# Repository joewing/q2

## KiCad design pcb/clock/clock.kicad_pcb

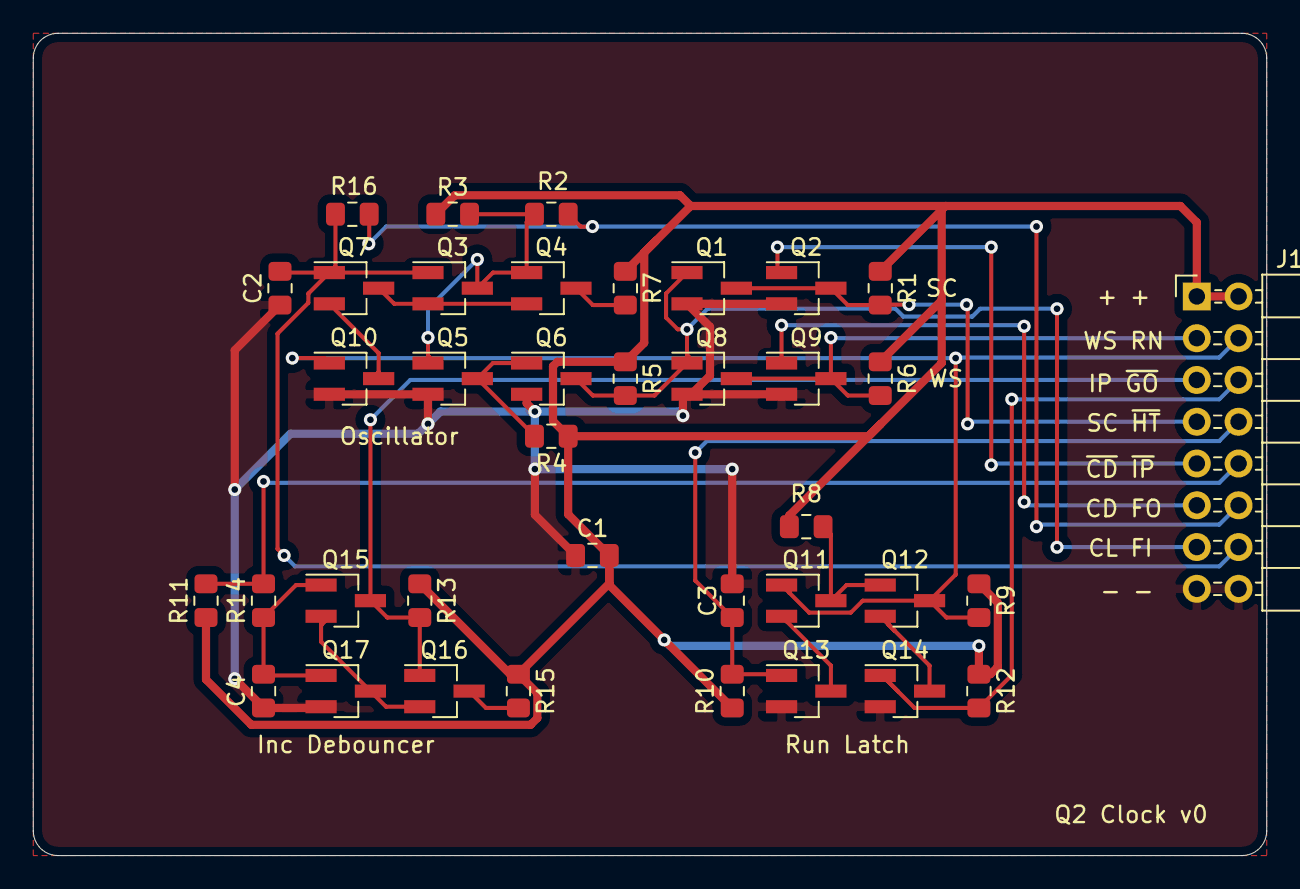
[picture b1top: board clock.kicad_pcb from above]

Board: 2 copper layers, 75.0 x 50.0 mm, 38 parts (0 on the bottom side), 25 nets.

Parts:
C1, C2, C3, C4: 0.1u; C_0805_2012Metric_Pad1.15x1.40mm_HandSolder
J1: Conn_02x08_Odd_Even; PinHeader_2x08_P2.54mm_Horizontal
Q1, Q2, Q3, Q4, Q5, Q6, Q7, Q8, Q9, Q10, Q11, Q12, Q13, Q14, Q15, Q16, Q17: 2N7002; SOT-23_Handsoldering
R1, R2, R3, R4, R5, R6, R7, R8, R9, R10, R11, R12, R13, R14, R15: 10k; R_0805_2012Metric_Pad1.15x1.40mm_HandSolder
R16: 1m; R_0805_2012Metric_Pad1.15x1.40mm_HandSolder

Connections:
CDIV: J1.11, Q9.1
CLK: J1.13, Q1.1, Q6.3, Q8.1, R5.2
FAST_IN: C2.2, J1.14, Q3.1, Q7.1, R16.2
FAST_OUT: J1.12, R2.1, R16.1
GND: C1.1, C2.1, C3.1, C4.1, J1.15, J1.16, Q1.2, Q2.2, Q5.2, Q6.2, Q8.2, Q9.2, Q10.2, Q13.2, Q14.2, Q17.2
INCP_DB: J1.5, Q15.3, Q16.1, R13.2
unnamed: C4.2, Q15.1, Q17.1, R14.1
unnamed: Q3.2, Q4.2, Q7.3
unnamed: Q3.3, Q4.1, Q5.1, R2.2, R3.2
unnamed: Q4.3, R7.2
unnamed: Q5.3, Q6.1, R4.2
unnamed: Q7.2, Q10.3
unnamed: Q11.2, Q13.3
unnamed: Q11.3, Q12.1, R8.2
unnamed: Q12.2, Q14.3
unnamed: Q15.2, Q16.2, Q17.3
unnamed: Q16.3, R15.2
RUN: J1.4, Q10.1, Q11.1, Q12.3, R9.2
SC: J1.7, Q1.3, Q2.3, R1.2
VCC: C1.2, J1.1, J1.2, R1.1, R3.1, R4.1, R5.1, R6.1, R7.1, R8.1, R9.1, R10.1, R11.1, R12.1, R13.1, R15.1
WS: J1.3, Q8.3, Q9.3, R6.2
~CDIV: J1.9, Q2.1
~INCP_SW: J1.10, R11.2, R14.2
~START_SW: J1.6, Q14.1, R12.2
~STOP_SW: C3.2, J1.8, Q13.1, R10.2

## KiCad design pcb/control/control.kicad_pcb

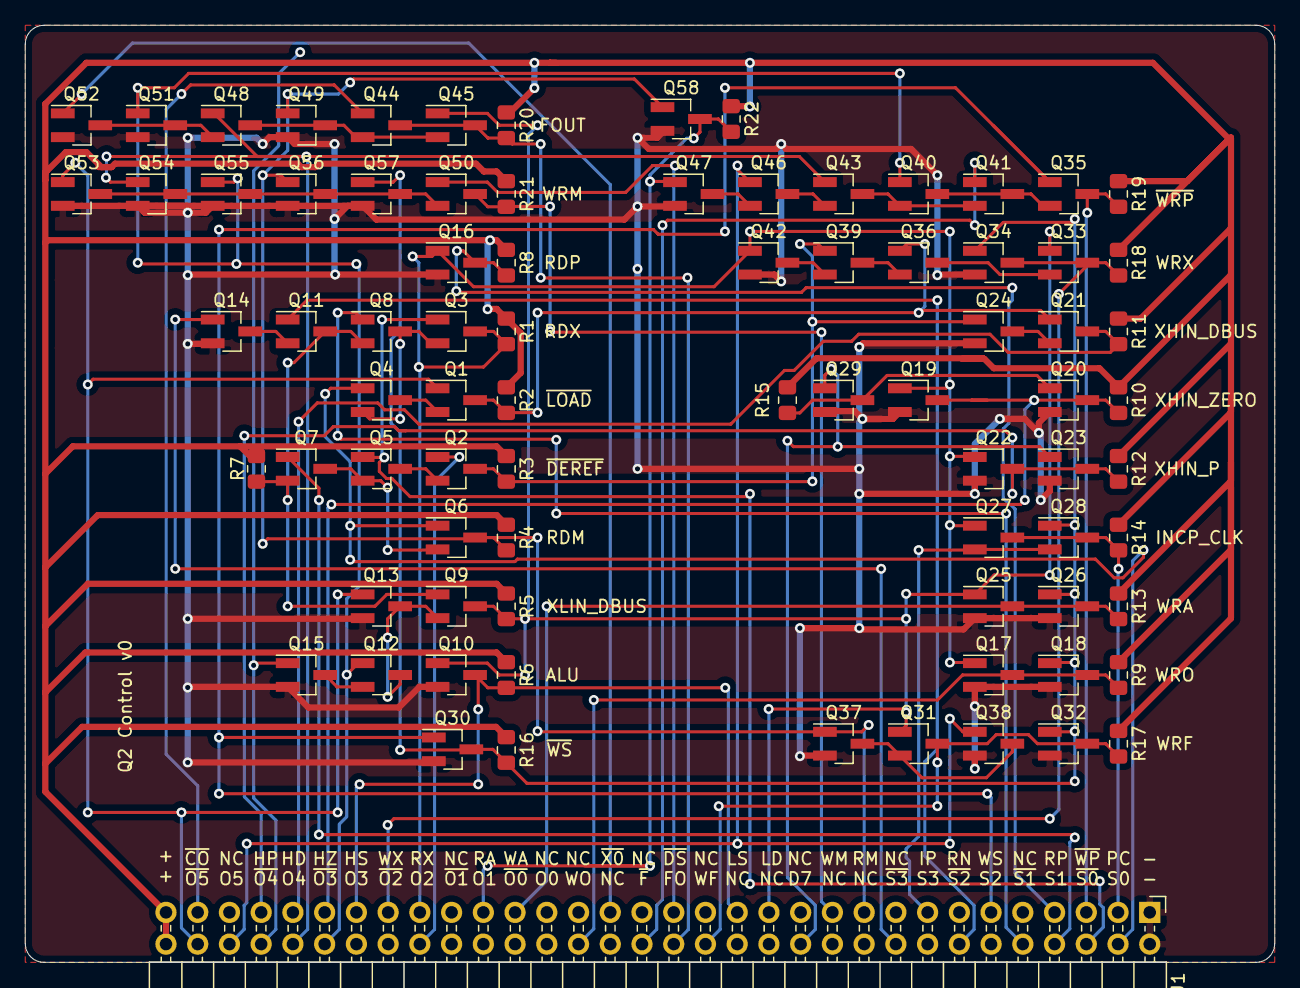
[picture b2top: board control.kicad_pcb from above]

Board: 2 copper layers, 100.0 x 75.0 mm, 81 parts (0 on the bottom side), 62 nets.

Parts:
J1: Conn_02x32_Odd_Even; PinHeader_2x32_P2.54mm_Horizontal
Q1, Q2, Q3, Q4, Q5, Q6, Q7, Q8, Q9, Q10, Q11, Q12, Q13, Q14, Q15, Q16, Q17, Q18, Q19, Q20, Q21, Q22, Q23, Q24, Q25, Q26, Q27, Q28, Q29, Q30, Q31, Q32, Q33, Q34, Q35, Q36, Q37, Q38, Q39, Q40, Q41, Q42, Q43, Q44, Q45, Q46, Q47, Q48, Q49, Q50, Q51, Q52, Q53, Q54, Q55, Q56, Q57, Q58: 2N7002; SOT-23_Handsoldering
R1, R2, R3, R4, R5, R6, R7, R8, R9, R10, R11, R12, R14, R15, R16, R17, R18, R19, R20, R21, R22: 10k; R_0805_2012Metric_Pad1.15x1.40mm_HandSolder
R13: 1k; R_0805_2012Metric_Pad1.15x1.40mm_HandSolder

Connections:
DBUS7: J1.24, Q23.1, Q29.1
FOUT: J1.32, Q44.3, Q45.3, R20.2
GND: J1.1, J1.2, Q10.2, Q13.2, Q14.2, Q15.2, Q16.2, Q17.2, Q18.2, Q19.2, Q20.2, Q22.2, Q23.2, Q24.2, Q25.2, Q26.2, Q29.2, Q30.2, Q32.2, Q34.2, Q37.2, Q38.2, Q42.2, Q47.2, Q49.2, Q51.2, Q52.2, Q53.2, Q54.2, Q55.2, Q56.2, Q57.2, Q58.2
INCP_CLK: J1.3, Q27.3, Q28.3, R14.2
INCP_DB: J1.15, Q27.2, Q28.2
unnamed: Q1.2, Q4.3
unnamed: Q2.2, Q5.3
unnamed: Q3.2, Q4.2, Q8.3
unnamed: Q5.2, Q6.2, Q7.3
unnamed: Q11.2, Q14.3
unnamed: Q7.2, Q8.2, Q9.1, Q11.3, R7.2
unnamed: Q12.2, Q15.3
unnamed: Q9.2, Q12.3, Q13.3
unnamed: Q21.2, Q24.3
unnamed: Q31.2, Q37.3, Q38.3
unnamed: Q33.2, Q36.3
unnamed: Q35.2, Q40.3, Q41.3
unnamed: Q36.2, Q39.3
unnamed: Q39.2, Q42.3
unnamed: Q40.2, Q41.2, Q43.3
unnamed: Q43.2, Q46.3
unnamed: Q44.2, Q45.2, Q48.3, Q49.3
unnamed: Q46.2, Q47.3
unnamed: Q48.2, Q51.3, Q52.3
unnamed: Q50.2, Q53.3, Q54.3, Q55.3, Q56.3, Q57.3
OP2: J1.48, Q2.1
OP4: J1.56, Q43.1, Q48.1, Q54.1
OP5: J1.60, Q38.1, Q46.1
RDA_DBUS: J1.43, Q47.1, Q58.3, R22.2
RDM: J1.19, Q6.3, Q37.1, Q49.1, Q56.1, Q58.1, R4.2
RDP_ABUS: J1.7, Q16.3, R8.2
RDX_ABUS: J1.47, Q3.3, Q16.1, Q17.1, Q19.1, Q22.1, Q27.1, Q42.1, R1.2
S0: J1.4, Q4.1, Q6.1
S1: J1.8, Q7.1
STATE_ALU: J1.27, J1.51, Q10.3, R6.2
VCC: J1.63, J1.64, R1.1, R2.1, R3.1, R4.1, R5.1, R6.1, R7.1, R8.1, R9.1, R10.1, R11.1, R12.1, R13.1, R14.1, R15.1, R16.1, R17.1, R18.1, R19.1, R20.1, R21.1, R22.1
WRA: J1.41, Q25.3, Q26.3, R13.2
WRF: J1.30, Q31.3, Q32.3, R17.2
WRM: J1.21, Q50.3, R21.2
WRO: J1.38, Q17.3, Q18.3, R9.2
WRX: J1.49, Q33.3, Q34.3, R18.2
WS: J1.11, Q30.1, Q35.1
XHIN_DBUS: J1.55, Q21.3, R11.2
XHIN_P: J1.57, Q22.3, Q23.3, R12.2
XHIN_ZERO: J1.53, Q19.3, Q20.3, R10.2
XLIN_DBUS: J1.25, Q9.3, Q10.1, Q25.1, Q31.1, Q33.1, Q45.1, R5.2
~ALU_COUT: J1.61, Q44.1
~DBUS7: Q20.1, Q29.3, R15.2
~DEP_SW: J1.31, Q50.1
~F: J1.34, Q41.1
~OP3: J1.54, Q12.1, Q40.1, Q51.1, Q55.1
~OP4: J1.58, Q15.1
~OP5: J1.62, Q1.1, Q13.1, Q53.1
~S0: J1.6, Q3.1, Q5.1
~S1: J1.10, Q8.1
~S2: J1.14, Q11.1
~S3: J1.18, Q14.1
~STATE_DEREF: Q2.3, Q24.1, Q39.1, R3.2
~STATE_LOAD: Q1.3, Q21.1, Q36.1, R2.2
~WRP: J1.5, Q35.3, R19.2
~WS: Q18.1, Q26.1, Q28.1, Q30.3, Q32.1, Q34.1, Q57.1, R16.2
~X0: J1.35, Q52.1

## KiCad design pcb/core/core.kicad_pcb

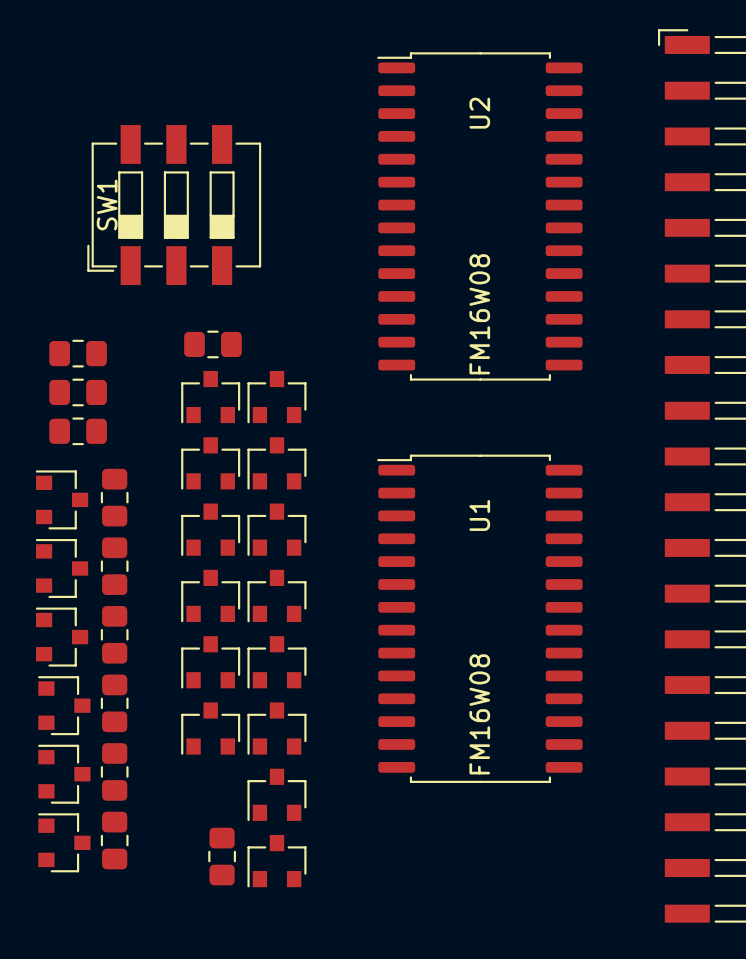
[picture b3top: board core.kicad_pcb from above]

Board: 2 copper layers, 36 parts (1 on the bottom side), 57 nets, no tracks yet.

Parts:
J1: Top; Harwin_M20-89020xx_1x20_P2.54mm_Horizontal
J2: Bottom; Harwin_M20-89020xx_1x20_P2.54mm_Horizontal
Q1, Q2, Q3, Q4, Q5, Q6, Q7, Q8, Q9, Q10, Q11, Q12, Q13, Q14, Q15, Q16, Q17, Q18, Q19, Q20: 2N7002; SOT-23
R1, R2, R3, R4, R5, R6, R7, R8, R9, R10, R11: R; R_0805_2012Metric_Pad1.15x1.40mm_HandSolder
SW1: SW_DIP_x03; SW_DIP_SPSTx03_Slide_6.7x9.18mm_W6.73mm_P2.54mm_LowProfile_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
U1, U2: FM16W08; SOIC-28W_7.5x17.9mm_P1.27mm

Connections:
A0: J1.17, U1.10, U2.10
A1: J1.16, U1.9, U2.9
A2: J1.15, U1.8, U2.8
A3: J1.14, U1.7, U2.7
A4: J1.13, U1.6, U2.6
A5: J1.12, U1.5, U2.5
A6: J1.11, U1.4, U2.4
A7: J1.10, U1.3, U2.3
A8: J1.9, U1.25, U2.25
A9: J1.8, U1.24, U2.24
A10: J1.7, U1.21, U2.21
A11: J1.6, U1.23, U2.23
A12: J1.5, U1.2, U2.2
A13: J1.4, Q8.1, Q14.1
A14: J1.3, Q9.1, Q13.1
A15: J1.2, Q4.1, Q19.1
D0: J2.4, U1.11
D1: J2.5, U1.12
D2: J2.6, U1.13
D3: J2.7, U1.15
D4: J2.8, U1.16
D5: J2.9, U1.17
D6: J2.10, U1.18
D7: J2.11, U1.19
D8: J2.12, U2.11
D9: J2.13, U2.12
D10: J2.14, U2.13
D11: J2.15, U2.15
D12: J2.16, U2.16
D13: J2.17, U2.17
D14: J2.18, U2.18
D15: J2.19, U2.19
GND: J1.20, J2.1, Q1.2, Q2.2, Q3.2, Q8.2, Q13.2, Q18.2, Q19.2, Q20.2, SW1.1, SW1.2, SW1.3, U1.14, U2.14
unnamed: Q4.2, Q6.3
unnamed: Q5.2, Q7.3
unnamed: Q10.2, Q12.3
unnamed: Q6.2, Q7.2, Q9.3, Q10.3
unnamed: Q11.2, Q12.2, Q14.3, Q15.3
unnamed: Q9.2, Q11.3
unnamed: Q14.2, Q16.3
unnamed: Q15.2, Q17.3
unnamed: Q16.2, Q17.2, Q18.3
unnamed: Q18.1, Q20.3, R11.2
S13: Q1.3, Q16.1, R1.2
S14: Q2.3, Q11.1, R2.2
S15: Q3.3, Q6.1, R3.2
VCC: J1.1, J2.20, R1.1, R2.1, R3.1, R4.1, R5.1, R6.1, R7.1, R8.1, R9.1, R10.1, R11.1, U1.28, U2.28
~A13: Q8.3, Q15.1, R8.2
~A14: Q10.1, Q13.3, R9.2
~A15: Q5.1, Q19.3, R10.2
~CE: Q4.3, Q5.3, R7.2, U1.20, U2.20
~EN: J1.18, Q20.1
~OE: J2.3, U1.22, U2.22
~S13: Q1.1, Q17.1, R4.2, SW1.6
~S14: Q2.1, Q12.1, R5.2, SW1.5
~S15: Q3.1, Q7.1, R6.2, SW1.4
~WE: J2.2, U1.27, U2.27

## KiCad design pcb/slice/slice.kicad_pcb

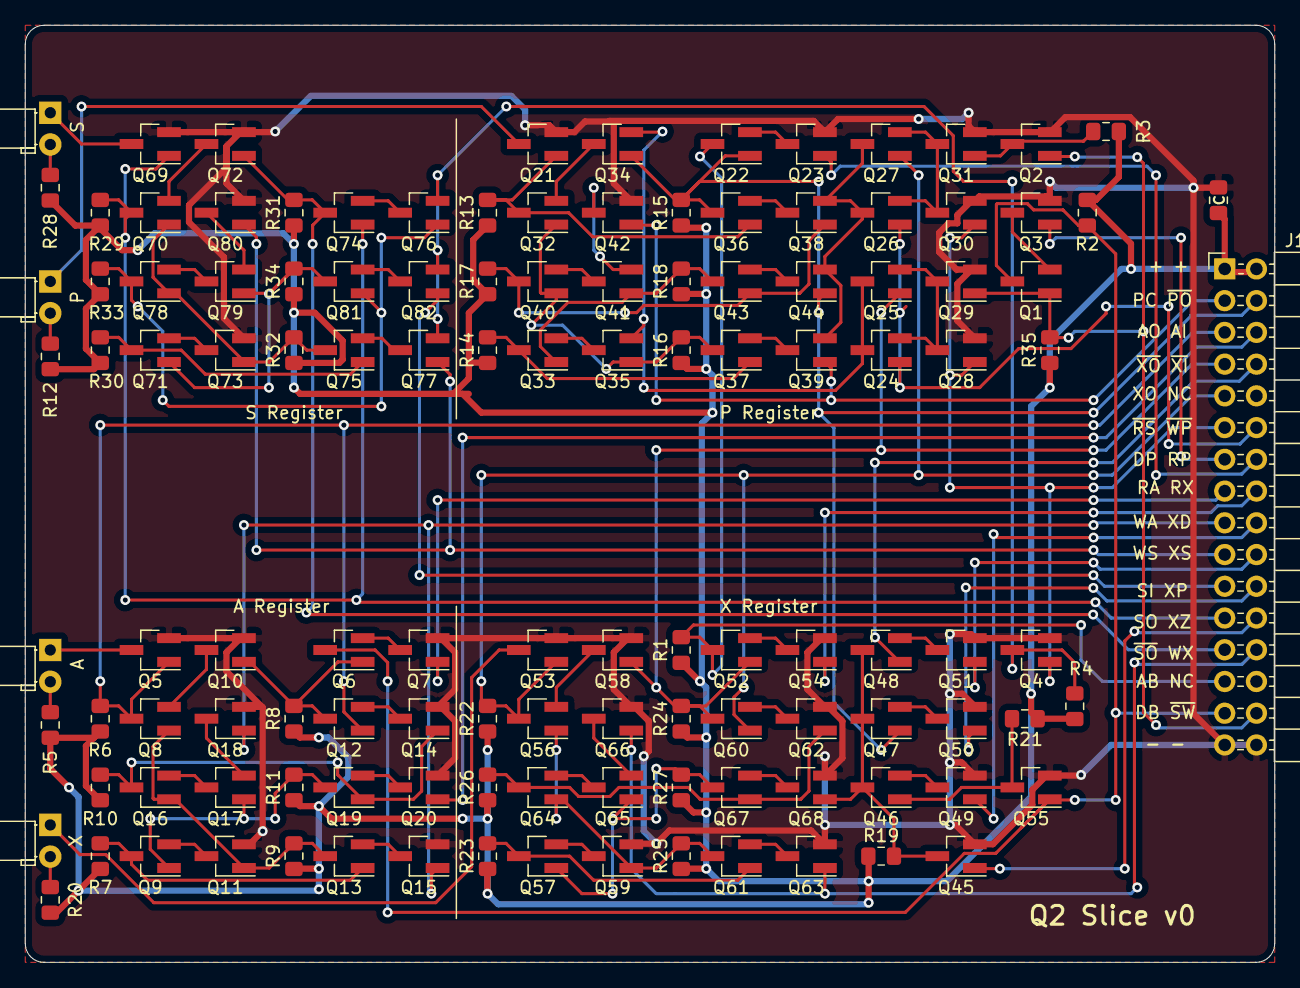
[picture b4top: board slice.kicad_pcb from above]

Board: 2 copper layers, 100.0 x 75.0 mm, 123 parts (0 on the bottom side), 97 nets.

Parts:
C1: 0.1u; C_0805_2012Metric_Pad1.15x1.40mm_HandSolder
D1: A; LED_D3.0mm_Horizontal_O1.27mm_Z2.0mm
D2: P; LED_D3.0mm_Horizontal_O1.27mm_Z2.0mm
D3: X; LED_D3.0mm_Horizontal_O1.27mm_Z2.0mm
D4: S; LED_D3.0mm_Horizontal_O1.27mm_Z2.0mm
J1: Conn_02x16_Odd_Even; PinHeader_2x16_P2.54mm_Horizontal
Q1, Q2, Q3, Q4, Q5, Q6, Q7, Q8, Q9, Q10, Q11, Q12, Q13, Q14, Q15, Q16, Q17, Q18, Q19, Q20, Q21, Q22, Q23, Q24, Q25, Q26, Q27, Q28, Q29, Q30, Q31, Q32, Q33, Q34, Q35, Q36, Q37, Q38, Q39, Q40, Q41, Q42, Q43, Q44, Q45, Q46, Q47, Q48, Q49, Q50, Q51, Q52, Q53, Q54, Q55, Q56, Q57, Q58, Q59, Q60, Q61, Q62, Q63, Q64, Q65, Q66, Q67, Q68, Q69, Q70, Q71, Q72, Q73, Q74, Q75, Q76, Q77, Q78, Q79, Q80, Q81, Q82: 2N7002; SOT-23_Handsoldering
R1, R2, R3, R4, R6, R7, R8, R9, R10, R11, R13, R14, R15, R16, R17, R18, R19, R21, R22, R23, R24, R25, R26, R27, R29, R30, R31, R32, R33, R34, R35: 10k; R_0805_2012Metric_Pad1.15x1.40mm_HandSolder
R5, R12, R20, R28: 1k; R_0805_2012Metric_Pad1.15x1.40mm_HandSolder

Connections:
/A Register/A DFF/~Q: Q6.1, Q10.1, Q12.3, R8.2
/X Register/X DFF/D: Q45.3, Q46.3, Q47.3, Q48.3, Q68.1, R19.2
ABUS: J1.27, Q22.3, Q52.3, R1.2
AIN: J1.6, Q20.1
AOUT: J1.5, Q5.1, Q8.3, Q12.1, R6.2
CLRP: Q26.3, Q27.3, Q38.2, Q39.2, Q44.2
DBUS: J1.29, Q1.3, Q6.3, Q55.1, R2.2
DEP: J1.13, Q3.1
GND: C1.2, J1.31, J1.32, Q2.2, Q3.2, Q4.2, Q5.2, Q7.2, Q10.2, Q11.2, Q14.2, Q15.2, Q18.2, Q20.2, Q21.2, Q23.2, Q28.2, Q29.2, Q30.2, Q31.2, Q42.2, Q45.2, Q49.2, Q50.2, Q51.2, Q53.2, Q54.2, Q55.2, Q58.2, Q59.2, Q62.2, Q63.2, Q66.2, Q68.2, Q69.2, Q72.2, Q73.2, Q80.2
INCP_CLK: J1.3, Q39.1, Q42.1
unnamed: D1.1, Q5.3
unnamed: D1.2, R5.2
unnamed: D2.1, Q21.3
unnamed: D2.2, R12.2
unnamed: D3.1, Q53.3
unnamed: D3.2, R20.2
unnamed: D4.1, Q69.3
unnamed: D4.2, R28.2
unnamed: Q1.2, Q3.3
unnamed: Q6.2, Q7.3
unnamed: Q8.2, Q10.3
unnamed: Q8.1, Q11.1, Q13.3, Q16.1, R9.2
unnamed: Q9.2, Q11.3
unnamed: Q12.2, Q14.3
unnamed: Q9.3, Q13.1, R7.2
unnamed: Q13.2, Q15.3
unnamed: Q14.1, Q16.3, Q19.1, R10.2
unnamed: Q16.2, Q17.3
unnamed: Q9.1, Q17.1, Q19.3, R11.2
unnamed: Q17.2, Q18.3
unnamed: Q19.2, Q20.3
unnamed: Q22.2, Q23.3
unnamed: Q24.2, Q25.2, Q28.3, Q29.3
unnamed: Q26.2, Q27.2, Q30.3, Q31.3
unnamed: Q32.1, Q35.1, Q37.3, Q40.1, R16.2
unnamed: Q32.2, Q34.3
unnamed: Q33.1, Q41.1, Q43.3, R18.2
unnamed: Q33.2, Q35.3
unnamed: Q33.3, Q37.1, R14.2
unnamed: Q36.2, Q38.3
unnamed: Q37.2, Q39.3
unnamed: Q38.1, Q40.3, Q43.1, R17.2
unnamed: Q40.2, Q41.3
unnamed: Q41.2, Q42.3
unnamed: Q43.2, Q44.3
unnamed: Q46.2, Q49.3
unnamed: Q47.2, Q50.3
unnamed: Q48.2, Q51.3
unnamed: Q52.2, Q54.3
unnamed: Q56.1, Q59.1, Q61.3, Q64.1, R25.2
unnamed: Q56.2, Q58.3
unnamed: Q57.1, Q65.1, Q67.3, R27.2
unnamed: Q57.2, Q59.3
unnamed: Q57.3, Q61.1, R23.2
unnamed: Q60.2, Q62.3
unnamed: Q61.2, Q63.3
unnamed: Q62.1, Q64.3, Q67.1, R26.2
unnamed: Q64.2, Q65.3
unnamed: Q65.2, Q66.3
unnamed: Q67.2, Q68.3
unnamed: Q70.1, Q73.1, Q75.3, Q78.1, R32.2
unnamed: Q70.2, Q72.3
unnamed: Q71.1, Q79.1, Q81.3, R34.2
unnamed: Q71.2, Q73.3
unnamed: Q71.3, Q75.1, R30.2
unnamed: Q74.2, Q76.3
unnamed: Q75.2, Q77.3
unnamed: Q76.1, Q78.3, Q81.1, R33.2
unnamed: Q78.2, Q79.3
unnamed: Q79.2, Q80.3
unnamed: Q81.2, Q82.3
P: Q21.1, Q32.3, Q36.1, R13.2
RDA_DBUS: J1.15, Q7.1
RDP_ABUS: J1.14, Q23.1
RDX_ABUS: J1.16, Q54.1
RST: Q4.3, Q76.2, Q77.2, Q82.2, R4.2
SETP: Q24.3, Q25.3, Q34.2, Q35.2
SIN: J1.21, Q82.1
SOUT: J1.23, Q69.1, Q70.3, Q74.1, R29.2
SW: Q2.3, Q31.1, R3.2
VCC: C1.1, J1.1, J1.2, R1.1, R2.1, R3.1, R4.1, R5.1, R6.1, R7.1, R8.1, R9.1, R10.1, R11.1, R12.1, R13.1, R14.1, R15.1, R16.1, R17.1, R18.1, R19.1, R20.1, R21.1, R22.1, R23.1, R24.1, R25.1, R26.1, R27.1, R28.1, R29.1, R30.1, R31.1, R32.1, R33.1, R34.1, R35.1
WRA: J1.17, Q15.1, Q18.1
WRS: J1.19, Q77.1, Q80.1
WRX: J1.26, Q63.1, Q66.1
XIN_DBUS: J1.18, Q49.1
XIN_P: J1.22, Q50.1
XIN_SHIFT: J1.20, Q51.1
XIN_ZERO: J1.24, Q45.1
XOUT: J1.9, Q27.1, Q53.1, Q56.3, Q60.1, R22.2
~DBUS: Q46.1, Q55.3, R21.2
~P: J1.4, Q22.1, Q34.1, Q36.3, Q44.1, Q47.1, R15.2
~RST: J1.11, Q4.1, Q28.1, Q30.1
~SOUT: J1.25, Q72.1, Q74.3, R31.2
~SW: J1.30, Q1.1, Q2.1, Q29.1, R35.2
~WRP: J1.12, Q24.1, Q26.1
~XIN: J1.8, Q48.1
~XOUT: J1.7, Q25.1, Q52.1, Q58.1, Q60.3, R24.2
